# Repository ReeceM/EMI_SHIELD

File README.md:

# EMI_SHIELD
EMI arduino style shield

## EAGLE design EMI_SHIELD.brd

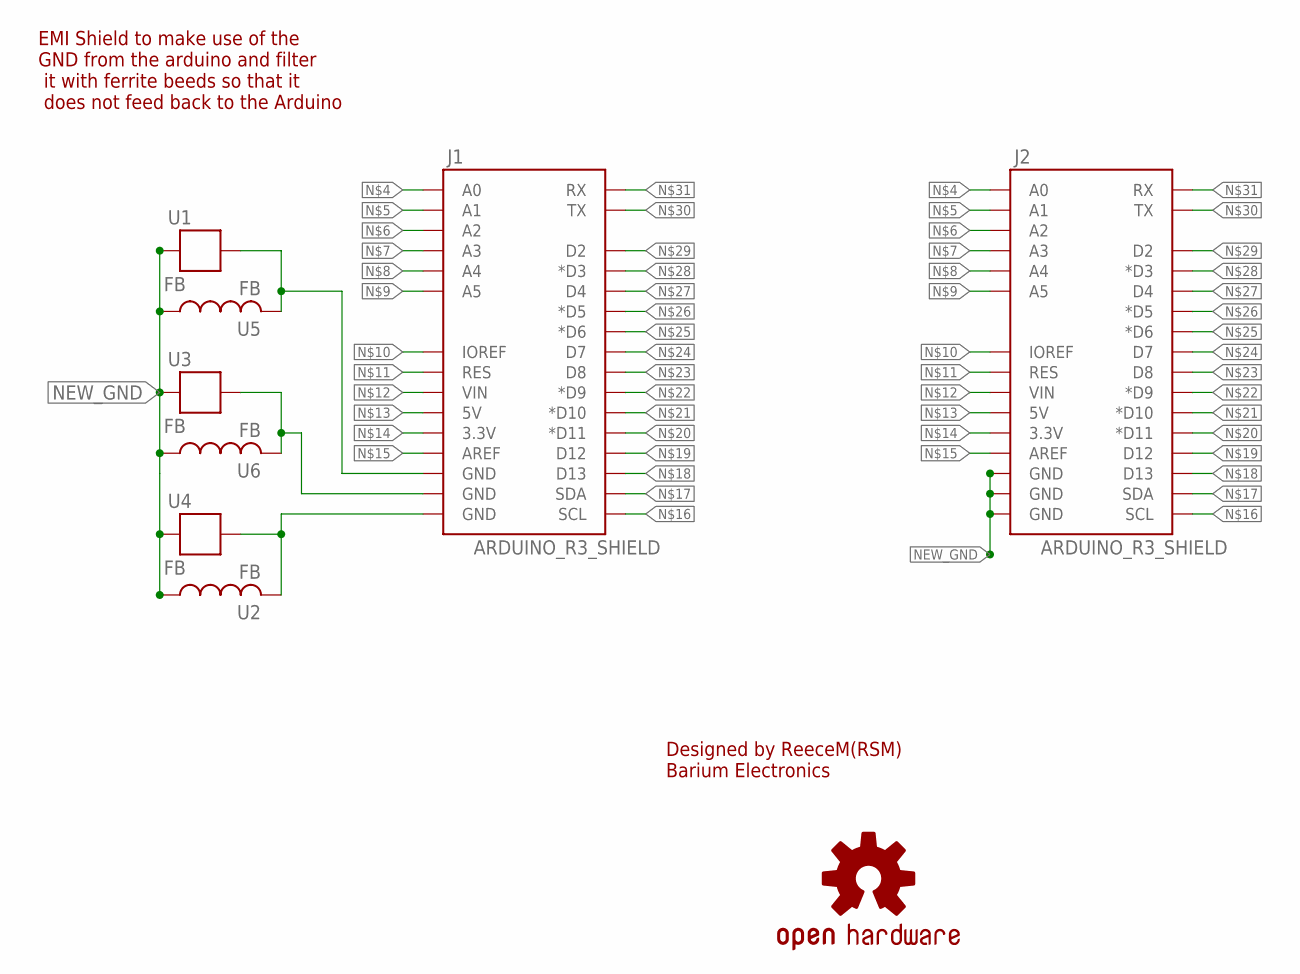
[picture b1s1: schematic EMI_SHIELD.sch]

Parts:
J1, J2: ARDUINO_R3_SHIELD; UNO_R3_SHIELD
LOGO1: OSHW-LOGOM-COPPER; OSHW-LOGO-M_COPPER
U1, U3, U4: FB; 0603
U2, U5, U6: FB

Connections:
unnamed: J1.GND@2 (GND), U1.1, U5.P$2 (2)
unnamed: J1.GND@1 (GND), U3.1, U6.P$2 (2)
unnamed: J1.GND@0 (GND), U2.P$2 (2), U4.1
unnamed: J1.A0, J2.A0
unnamed: J1.A1, J2.A1
unnamed: J1.A2, J2.A2
unnamed: J1.A3, J2.A3
unnamed: J1.A4, J2.A4
unnamed: J1.A5, J2.A5
unnamed: J1.IOREF, J2.IOREF
unnamed: J1.RES, J2.RES
unnamed: J1.VIN, J2.VIN
unnamed: J1.5V, J2.5V
unnamed: J1.3.3V, J2.3.3V
unnamed: J1.AREF, J2.AREF
unnamed: J1.SCL, J2.SCL
unnamed: J1.SDA, J2.SDA
unnamed: J1.D13, J2.D13
unnamed: J1.D12, J2.D12
unnamed: J1.D11 (*D11), J2.D11 (*D11)
unnamed: J1.D10 (*D10), J2.D10 (*D10)
unnamed: J1.D9 (*D9), J2.D9 (*D9)
unnamed: J1.D8, J2.D8
unnamed: J1.D7, J2.D7
unnamed: J1.D6 (*D6), J2.D6 (*D6)
unnamed: J1.D5 (*D5), J2.D5 (*D5)
unnamed: J1.D4, J2.D4
unnamed: J1.D3 (*D3), J2.D3 (*D3)
unnamed: J1.D2, J2.D2
unnamed: J1.TX, J2.TX
unnamed: J1.RX, J2.RX
NEW_GND: J2.GND@0 (GND), J2.GND@1 (GND), J2.GND@2 (GND), U1.2, U2.P$1 (1), U3.2, U4.2, U5.P$1 (1), U6.P$1 (1)

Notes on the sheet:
EMI Shield to make use of the GND from the arduino and filter it with ferrite beeds so that it does not feed back to the Arduino
Designed by ReeceM(RSM) Barium Electronics

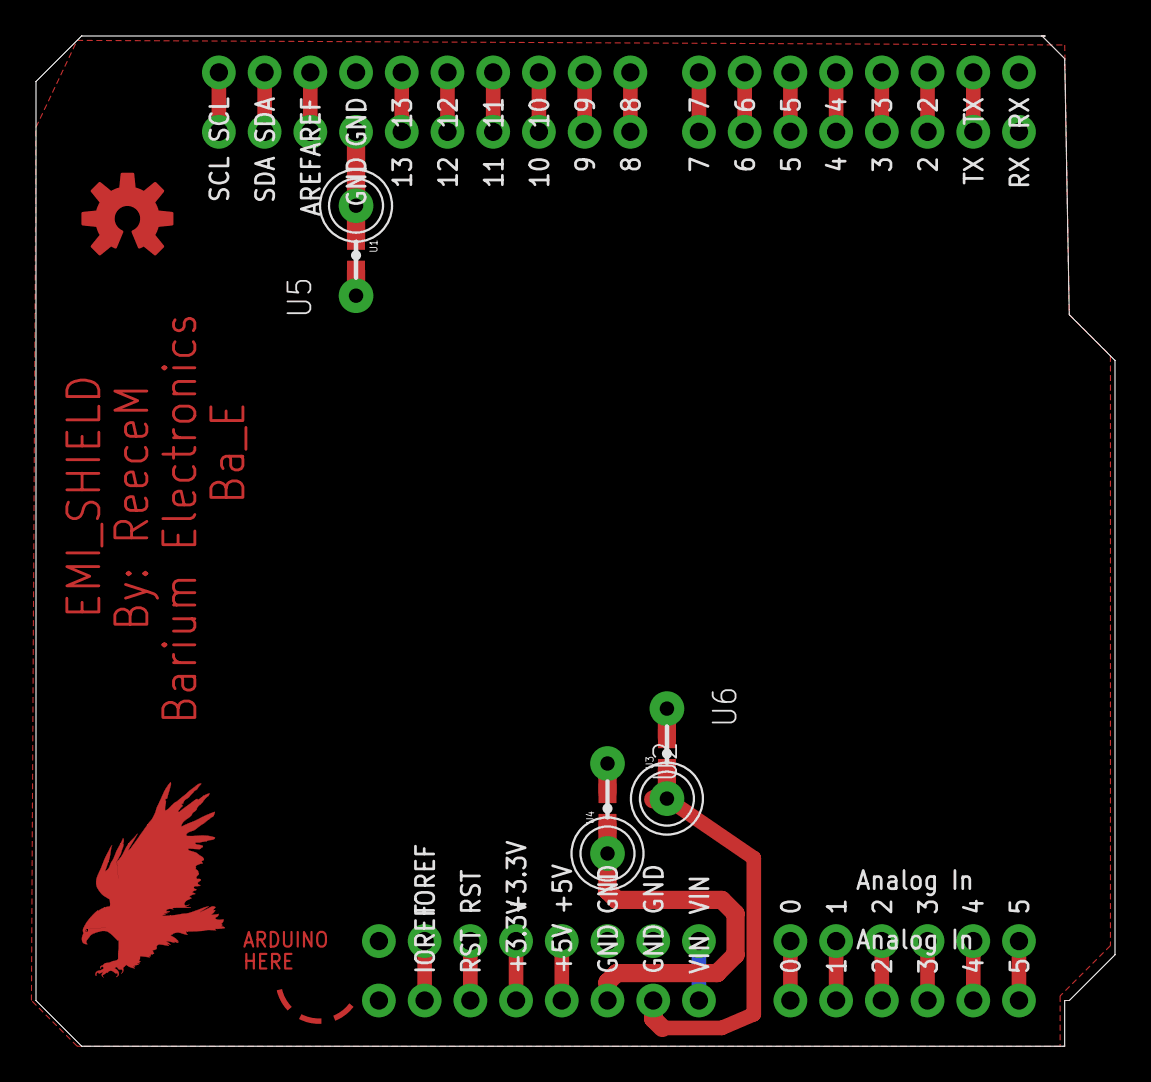
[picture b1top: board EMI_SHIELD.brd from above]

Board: 2 copper layers, 59.9 x 56.1 mm, 10 parts (0 on the bottom side), 32 nets.

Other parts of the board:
U$1: EAGLE-TOP-8MM

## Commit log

2016-10-13 Create board
2016-10-13 Add files via upload
    Includes the auto backups
2016-10-13 Put into folders

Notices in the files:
parts and their libraries:
SparkFun-Boards: Licensing: Creative Commons ShareAlike 4.0 International - https://creativecommons.org/licenses/by-sa/4.0
